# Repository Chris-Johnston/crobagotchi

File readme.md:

# Crobagotchi

Raise your own _virtual_ crow!

## What?

_Crobagotchi_ combines [Tamagotchi] with the [Crow of Judgement] (also referred to as a "Crob").

It's a portable handheld virtual pet which runs on an ATTiny85 and uses a SSD1306 OLED display
powered by a coin cell battery. The custom boards were designed using KiCad and [svg2mod], and the sprite work was done with Aseprite, GIMP, and [image2cpp].

## Why?

[Last year I made a PCB Crow of Judgement](https://github.com/Chris-Johnston/CrowOfJudgement), and this year I wanted to iterate on that. Eventually, I got the idea to make a knockoff Tamagotchi, and so I figured this would be a great time to do so.

[I still did make a simpler ornament this year, in the shape of an snowflake.](https://github.com/Chris-Johnston/snowflake-ornament) A lof of the board design is similar, it also uses ATTiny85.

## What else?

Battery life was a key concern, and so for this project I put a fair bit of time in to make sure
that wouldn't be a problem.

- Data is saved to EEPROM, so if the battery dies the state is preserved.
- Features of the ATTiny85 are disabled when unused, like the ADC.
- I use the deep sleep mode combined with the Watchdog Timer Interrupt to track realtime seconds (ticks once every 8 seconds), so that real time gets tracked as the device is sleeping.
- The SSD1306 is shut off as well during sleep to conserve power.

The other big issue was flash storage. The ATTiny85 has 8k of flash, which is largest offered.
I did not implement any compression for sprite bitmaps, which for each byte represents 8 vertical pixels. The 48x48 pixel image of the crow is 288 bytes, there were several times when testing where I used literally every last byte available in flash.

This code is pretty messy, I have not put much effort into cleaning it up as that was not a concern.

### SSD1306 Trouble

My experience with the SSD1306 with ATTiny85 was interesting. I tried a few libraries over time, and eventually settled with [Tiny4kOLED]. This one offered a sensible library that introduce extra fluff, like a menu that I'd never use?

Most importantly, I found that there was a bit-bang i2c implementation available where I could
reassign the pins. This was very important, because I had already ordered boards which relied
on a different pinout (PCBWay took a solid month to order), and I didn't want to disconnect
the display each time I reflashed it.

I copied this bitbang implementation and modified it to use the pins I specified.

Turns out there was more than one modification I'd make to this library. It included a 6x8 px font
which was great, but there were characters that I didn't use. Because of this, I modified
this font to add extra symbols that I'd use elsewhere, without having to add more to the flash.

## Pictures / Assembly Instructions

Here's the board fully assembled:

Mind the flux and stray bits of q-tip used to clean it up.

1. First, unless already soldered, solder the ATTiny85 to the board.
To do this, I like to start by tinning pin 1, placing the IC in the right spot,
and sticking the IC in place. Then, doing the rest of the pins isn't much extra effort. Any extra solder can be removed with solder wick.

2. Then solder the surface mount components.

    | Label | Value |
    | -- | -- |
    | C1 | 0.1 uF 1206 Capacitor |
    | R1 | 10k 1206 Resistor |
    | R2, R3 | 4.7k 1206 Resistor |

    I use a similar method, where I tin one side, place the part, solder that side down, and then solder the remaining side.

3. Then, install the 6mm push buttons. These are straightforward.

4. Install the battery holder. The square side is the positive terminal on the battery holders I used. **This must go on before the display!**

    Be sure to clip the longer (and very sharp) pins of the battery holder.

    Before installing the display, I added some electrical tape to cover the battery contacts. This is so that it doesn't accidentally touch the display.

5. Install the display. There is some gap between the board and the display, and so I tilt the display a bit.

6. Finally, I used rubbing alcohol and q-tips to help clean up some of the flux.

7. To program the board, if it isn't already, I used a typical 6 pin USB AVR programmer **running at 3.3 volts**. While the ATTiny85 can run at 5v, the screen cannot. An [Arduino as ISP](https://www.arduino.cc/en/Tutorial/BuiltInExamples/ArduinoISP) can work great too.

    Because I didn't want pins sticking up the entire time, I could jam the pins at
    an angle to help a bit.

    When programming you'll need to do a few things:
      - Install ATTiny85 support via the board manager using https://github.com/damellis/attiny
      - Set the clock to "Internal 1 MHz" in the board settings
      - Click "burn bootloader" to set the clock speed

    Then, upload the firmware to the board.

8. Finally I could stick the battery in.

[Tamagotchi]: https://en.wikipedia.org/wiki/Tamagotchi
[Crow of Judgement]: https://knowyourmeme.com/memes/crow-of-judgement
[svg2mod]: https://github.com/svg2mod/svg2mod
[image2cpp]: https://javl.github.io/image2cpp/
[Tiny4kOLED]: https://github.com/datacute/Tiny4kOLED

## Instructions

On first boot, a new Crob will be created with a randomly selected name.
You'll want to feed and play with it every day using the buttons to wake up
the device from sleep.

If for any reason you need a new Crob, hold the A + B buttons for a moment until a menu displays. Hold A in that menu, and you'll get a new crow.

If the battery dies all of your progress will be saved in the internal EEPROM.
The reset jumper on the back (don't solder it!) can be used in case something
crashes.

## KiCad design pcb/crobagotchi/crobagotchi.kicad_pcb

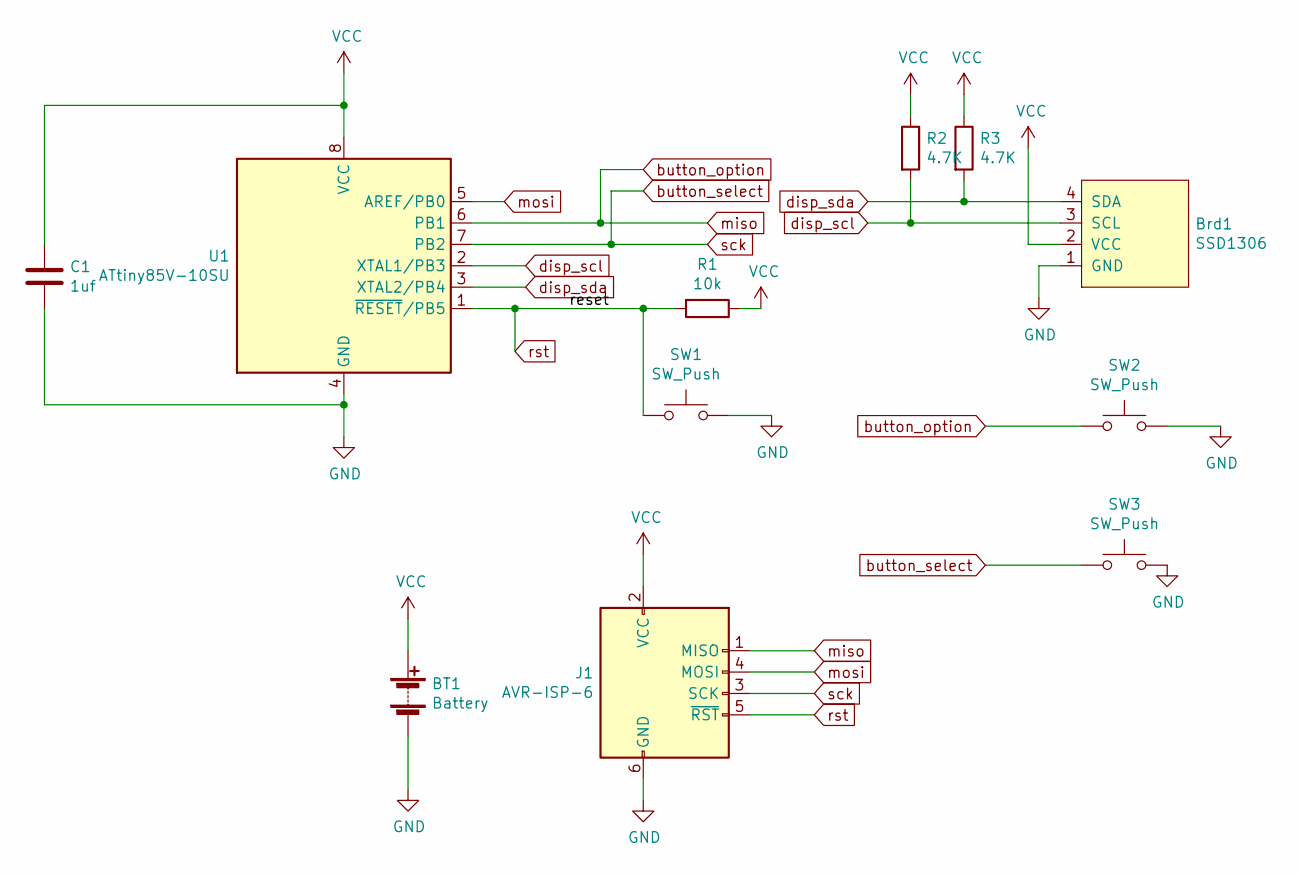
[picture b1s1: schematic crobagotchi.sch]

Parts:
BT1: Battery; BatteryHolder_ComfortableElectronic_CH273-2450_1x2450
Brd1: SSD1306; 128x64OLED
C1: 1uf; C_1206_3216Metric_Pad1.42x1.75mm_HandSolder
J1: AVR-ISP-6; PinHeader_2x03_P2.54mm_Vertical
R1: 10k; R_1206_3216Metric_Pad1.42x1.75mm_HandSolder
R2, R3: 4.7K; R_1206_3216Metric_Pad1.42x1.75mm_HandSolder
SW1: SW_Push; SolderJumper-2_P1.3mm_Open_Pad1.0x1.5mm
SW2, SW3: SW_Push; SW_PUSH_6mm
U1: ATtiny85V-10SU; SOIJ-8_5.3x5.3mm_P1.27mm

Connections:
GND: BT1.2 (-), Brd1.1 (GND), C1.2, J1.6 (GND), SW1.2, SW2.2, SW3.2, U1.4 (GND)
VCC: BT1.1 (+), Brd1.2 (VCC), C1.1, J1.2 (VCC), R1.1, R2.1, R3.1, U1.8 (VCC)
button_option: J1.1 (MISO), SW2.1, U1.6 (PB1)
button_select: J1.3 (SCK), SW3.1, U1.7 (PB2)
disp_scl: Brd1.3 (SCL), R2.2, U1.2 (XTAL1/PB3)
disp_sda: Brd1.4 (SDA), R3.2, U1.3 (XTAL2/PB4)
mosi: J1.4 (MOSI), U1.5 (AREF/PB0)
rst: J1.5 (~RST), R1.2, SW1.1, U1.1 (~RESET~/PB5)

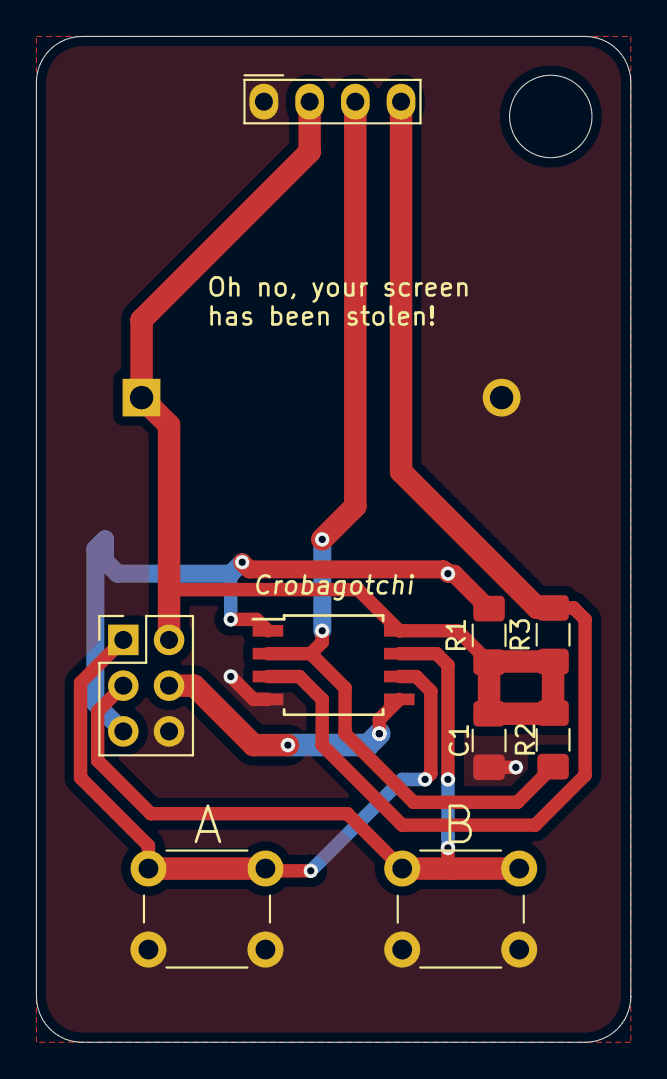
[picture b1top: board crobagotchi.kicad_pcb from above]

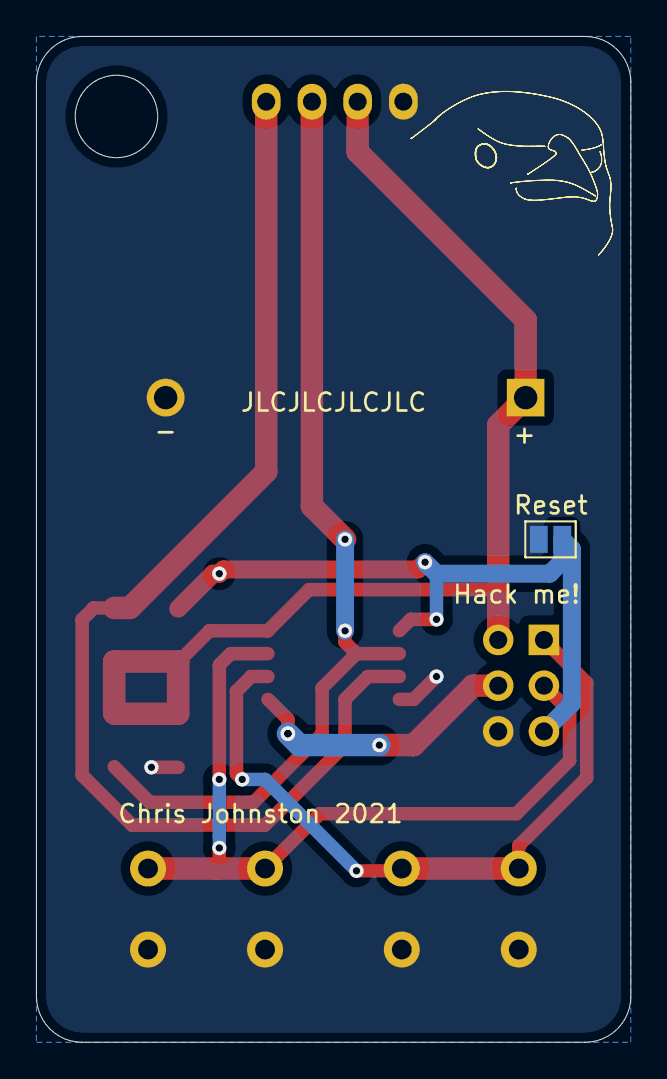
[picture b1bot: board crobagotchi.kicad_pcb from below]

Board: 2 copper layers, 33.0 x 55.9 mm, 12 parts (3 on the bottom side), 8 nets.

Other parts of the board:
svg2mod: G***; kicad_vectorcrob

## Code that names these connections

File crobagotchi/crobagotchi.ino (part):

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// #include "nano_gfx.h"
#include "sprites.h"

#define BITBANG_SCL PB3
#define BITBANG_SDA PB4

#include "Tiny4kOLED_bitbang_mod.h"
#include "font6x8caps_mod.h"
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  ADCSRA = 0; // ADC Control Status Register A (reg B does not have an enable bit)
  PRR &= 0b1110; // disable ADC
  pinMode(BUTTON_A, INPUT_PULLUP);
  pinMode(BUTTON_B, INPUT_PULLUP); // pb2 pb1

  // unreachable code
  //   if (watchdogInterrupt) // watchdog interrupt will reset
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
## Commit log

2021-11-07 add a bunch of hacky code
2021-11-07 8 second wd timer
2021-11-13 update pcb
2021-11-13 add gerber files that were made
2021-12-01 messy commit of current changes
2021-12-03 aaaaaaaaaaaa
2021-12-05 add a bunch of stuff and use up every byte
2021-12-07 free up some bytes
2021-12-09 fix bug where on sleep, it wakes up again
2021-12-09 comment out unused sprites
2021-12-22 add "b" emoji to font and name that uses it
2021-12-22 cleanup unused files
2021-12-22 add readme
2021-12-22 add todo
2021-12-22 remove unused files
2021-12-22 update gitignore
2021-12-22 apply gitignore
2021-12-22 Create LICENSE
2021-12-22 add unused qmake file
2021-12-26 add documentation
2021-12-26 add operation instructions
2022-01-06 add another option for sprites
